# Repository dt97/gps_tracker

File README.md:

# gps_tracker
GPS Tracker to track your whereabouts anywhere and anytime

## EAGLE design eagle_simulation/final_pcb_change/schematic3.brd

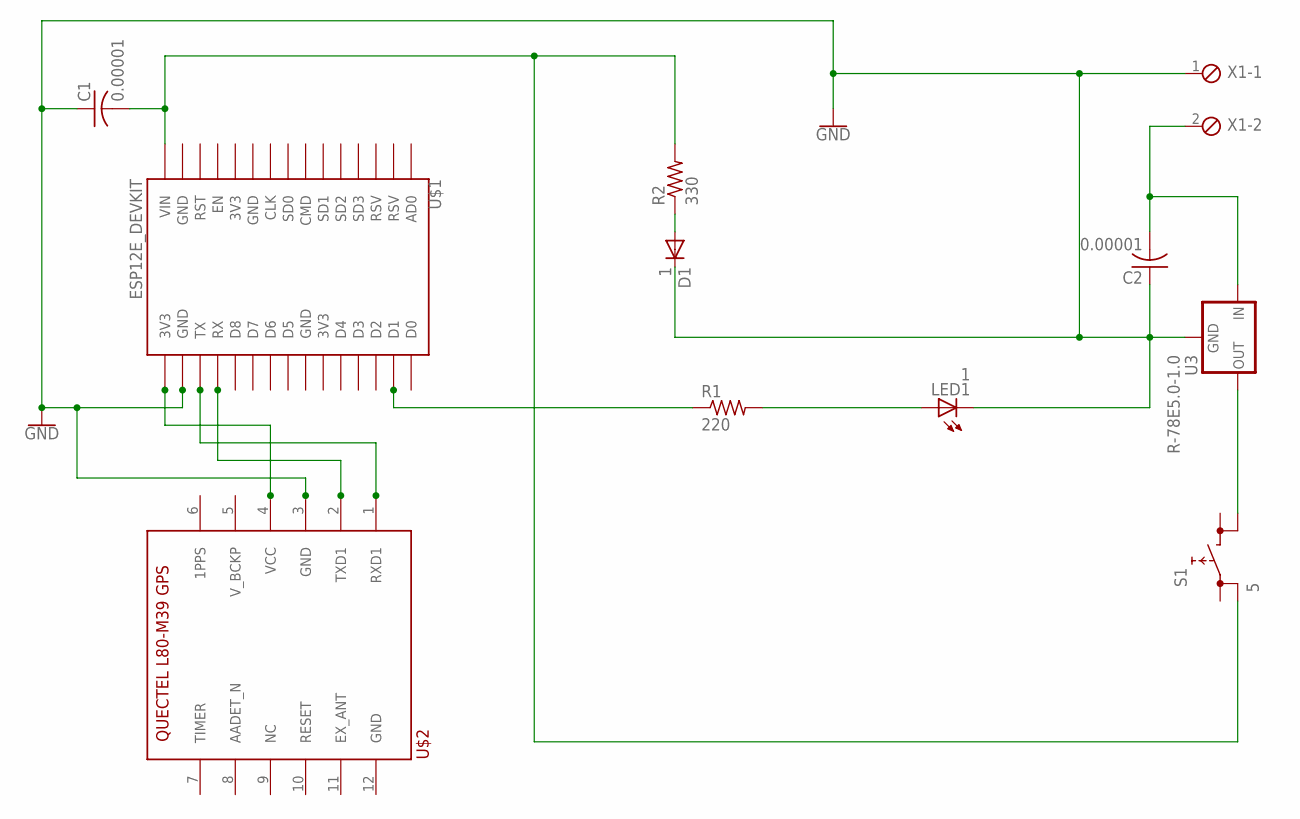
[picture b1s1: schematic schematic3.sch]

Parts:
C1, C2: 0.00001; C050-025X075
D1: 1; DO41-10
LED1: 1; LED5MM
R1: 220; 0204/7
R2: 330; 0204/7
S1: 5; REKN
U3: R-78E5.0-1.0; DC-DC_CONVERTER_78XX
U$1: ESP12E_DEVKIT
U$2: L80_GNSS_MODULE; L80_PACKAGE
X1: MPT2; 2POL254

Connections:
GND: C1.1, C2.1, D1.C, LED1.K (C), U3.GND, U$1.GND@3 (GND), U$2.3 (GND), X1.1
unnamed: D1.A, R2.1
unnamed: C2.2, U3.VIN (IN), X1.2
unnamed: S1.1B (1), U3.VOUT (OUT)
unnamed: R1.1, U$1.D1
unnamed: U$1.3V3@2 (3V3), U$2.4 (VCC)
unnamed: C1.2, R2.2, S1.0B (0), U$1.VIN
unnamed: LED1.A, R1.2
unnamed: U$1.RX, U$2.2 (TXD1)
unnamed: U$1.TX, U$2.1 (RXD1)

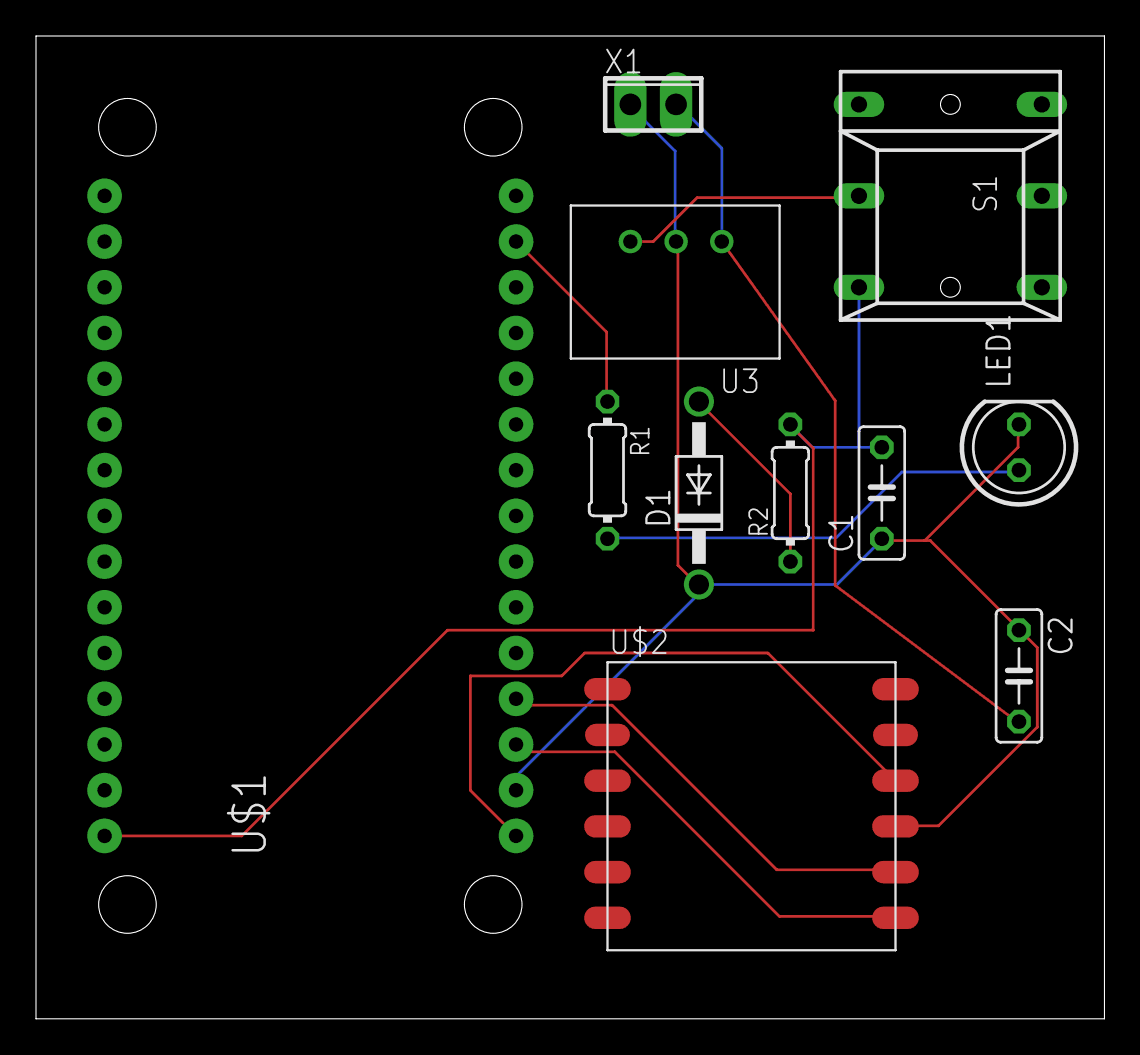
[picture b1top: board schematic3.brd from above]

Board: 2 copper layers, 59.4 x 54.6 mm, 11 parts (0 on the bottom side), 10 nets.

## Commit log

2018-05-22 intial commit
2018-05-22 delete_gps_info.php added to gps_tracker_php_codes
2018-05-23 Added gps_tacker_website_layout.docx file
2018-05-23 Initial edit
2018-05-23 add_user.php and other files edited to include email entry of all users and admins
2018-05-24 about_project.txt added to branch1
2018-05-24 added forgot_password.php and edited some files
2018-05-25 Added reset_password and other files in branch1
2018-05-29 added reset_password edited
2018-05-29 gps tracker database edited
2018-05-30 added eagle schematic of gps_tracker circuit
2018-05-30 added pcb layout for gps tracker
2018-05-31 added edited schematic of gps_tracker with quectel l80 gps_module added
2018-05-31 third edit to schematic and pcb
2018-05-31 final pcb layout files added
2018-06-01 made changes in gps_configure.ino file
2018-06-04 edited gps_configure2.ino
2018-06-06 edited tracker_website_layout.docx
2018-06-06 removed unnecessary files
2018-06-06 edited forgot_password page
2018-06-06 edited gps_info page and forgot_password page
2018-06-06 edited send_gps_info.php commands.txt and added send_gps_infoedit.php
2018-06-07 added gps_tracker_send_data.ino file
2018-06-08 added current_gps_info.php page
2018-06-08 edited current_gps_info.php page and commands.txt
2018-06-09 edited pcb layout if gps_tracker circuit
2018-06-11 added gps_tracker_configure3.ino
2018-06-17 edited eagle board file
2018-06-18 edited gps_tracker homepage content
2018-06-25 edited forgot-password.php and added some files
2018-06-26 added edited forgot_password page
2018-06-29 edited gps_tracker_layout

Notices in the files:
parts and their libraries:
SparkFun-IC-Power: Licensing: Creative Commons ShareAlike 4.0 International - https://creativecommons.org/licenses/by-sa/4.0
